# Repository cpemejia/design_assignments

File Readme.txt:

Student Name:  Elmer Mejia
Student #:     5003824808
Student Email: mejiae4@unlv.nevada.edu

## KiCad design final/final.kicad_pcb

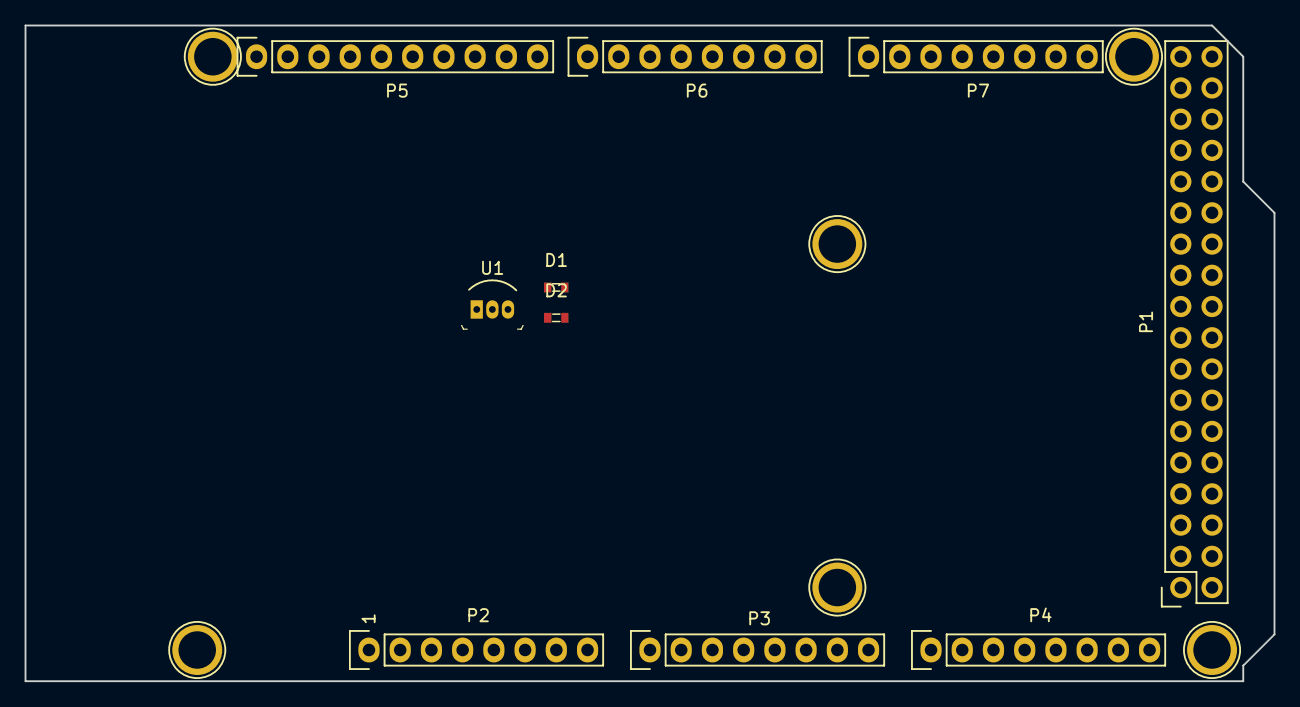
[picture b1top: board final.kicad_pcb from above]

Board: 2 copper layers, 101.6 x 53.3 mm, 16 parts (0 on the bottom side), 4 nets, no tracks yet.

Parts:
D1, D2: LTST-C193TGKT-5A; 0603
P1: Digital; Socket_Strip_Arduino_2x18
P2: Power; Socket_Strip_Arduino_1x08
P3, P4: Analog; Socket_Strip_Arduino_1x08
P5: PWM; Socket_Strip_Arduino_1x10
P6: PWM; Socket_Strip_Arduino_1x08
P7: Communication; Socket_Strip_Arduino_1x08
P8, P9, P10, P11, P12, P13: CONN_01X01; Arduino_1pin
U1: LM34DZ_NOPB; TO-92-3

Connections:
+5V: P1.35, P1.36, P2.5, U1.3
/34: D2.2, P1.21
/36: D1.2, P1.19
GND: P1.1, P1.2, P2.6, P2.7, P5.4, U1.1

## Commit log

2021-02-25 Create DA_2A_T1
2021-03-01 Rename DA_2A.c to DA_2AT1.c
2021-03-01 Rename DA_2AT1.c to DA_2AT2t.c
2021-03-01 Rename DA_2AT2.c to DA_2AT1.c
2021-03-30 Rename vid link.txt to vidlink.txt
2021-04-13 Rename DA_4b2.c to DA_4B2.c
